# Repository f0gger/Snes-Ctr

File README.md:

# SNES Controller – KiCad Hardware Design

KiCad hardware design files for a custom Super Nintendo Entertainment System (SNES) controller built around the ATmega328P microcontroller, with I²C communication for interfacing with external devices.

## Repository Structure

```text
Snes-Ctr/
├── gerbers/ - Gerber and drill files for PCB manufacturing.
│   ├── Snes-Ctr-B_Cu.gbl
│   ├── Snes-Ctr-B_Mask.gbs
│   ├── Snes-Ctr-B_Paste.gbp
│   ├── Snes-Ctr-B_Silkscreen.gbo
│   ├── Snes-Ctr-Edge_Cuts.gm1
│   ├── Snes-Ctr-F_Cu.gtl
│   ├── Snes-Ctr-F_Mask.gts
│   ├── Snes-Ctr-F_Paste.gtp
│   ├── Snes-Ctr-F_Silkscreen.gto
│   ├── Snes-Ctr-NPTH.drl
│   ├── Snes-Ctr-PTH.drl
│   └── Snes_Ctr_gerbers.zip
├── Snes-Ctr.kicad_dru - Custom PCB design rules
├── Snes-Ctr.kicad_pcb - PCB layout.
├── Snes-Ctr.kicad_pro - KiCad project configuration.
├── Snes-Ctr.kicad_sch - Circuit schematic.
└── README.md
```

File names and structure may vary depending on the actual project files.
Hardware Overview

The controller uses the ATmega328P to interface with the SNES controller inputs and handle communication with external hardware over the I²C bus.

The KiCad project contains the circuit schematic and PCB design, providing a starting point for reviewing, modifying, and manufacturing the hardware.
Requirements

    KiCad — for viewing and editing the schematic and PCB
    ATmega328P-compatible programming hardware — for flashing firmware, if applicable

## Getting Started

    Clone this repository:
    git clone <repository-url>
    cd <repository-directory>
    
    Open the .kicad_pro file in KiCad.
    Review the schematic (.kicad_sch) to understand the circuit.
    Open the PCB editor to inspect or modify the board layout.
    Run the electrical rules check (ERC) and design rules check (DRC) before manufacturing.

## Manufacturing

Before ordering or assembling the PCB:

    - Verify the schematic and PCB design.
    - Check component footprints and pin assignments.
    - Run ERC and DRC in KiCad.
    - Generate Gerber files and drill files using KiCad's fabrication tools.
    - Confirm the bill of materials (BOM) and component availability.

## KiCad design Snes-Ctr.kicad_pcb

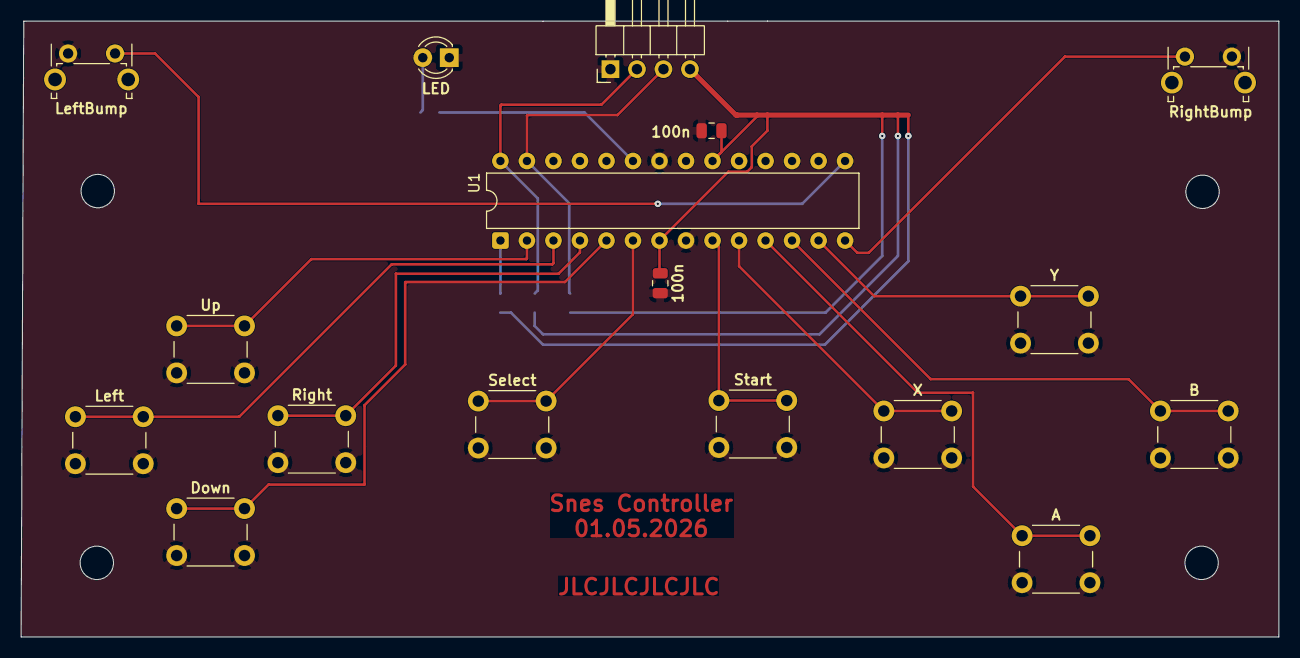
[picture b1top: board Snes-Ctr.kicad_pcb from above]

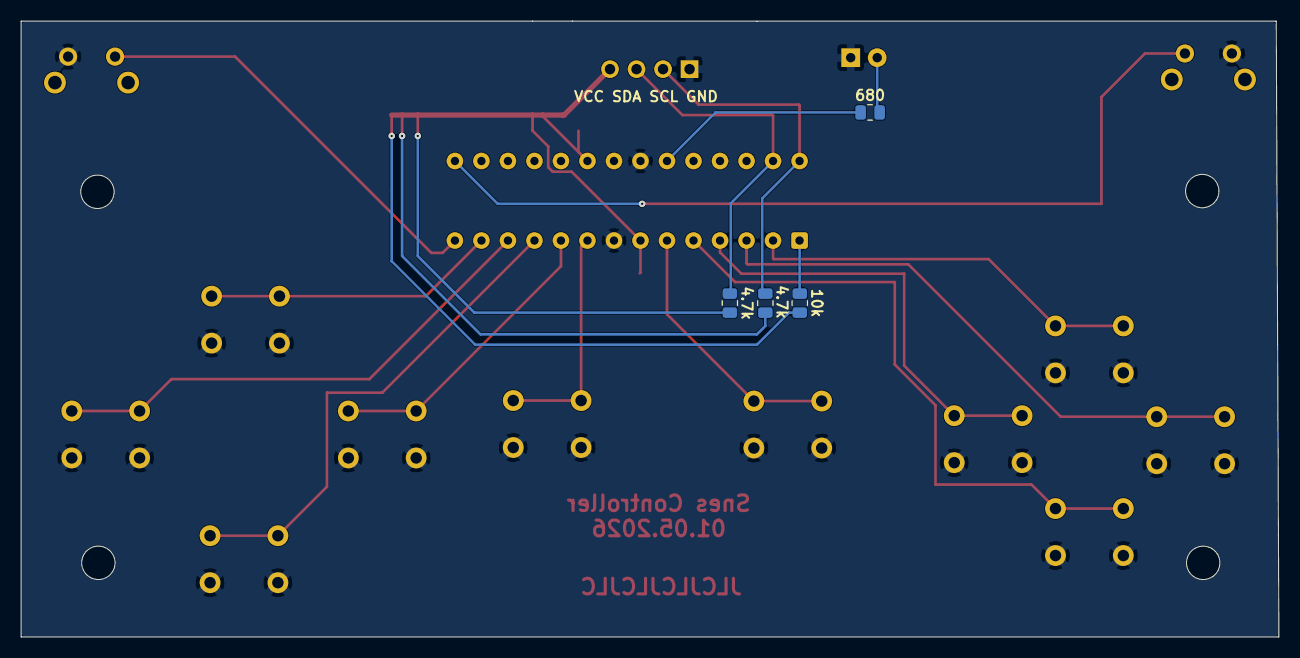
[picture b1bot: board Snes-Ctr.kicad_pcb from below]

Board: 2 copper layers, 120.5 x 59.0 mm, 21 parts (4 on the bottom side), 19 nets.

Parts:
4.7k, 4.7k#2: 4.7k; R_0805_2012Metric
10k: 10k; R_0805_2012Metric
100n, 100n#2: 100n; C_0805_2012Metric
680: 680; R_0805_2012Metric
A: A; SW_PUSH_6mm_H7.3mm
B: B; SW_PUSH_6mm_H7.3mm
Down: Down; SW_PUSH_6mm_H7.3mm
LED: LED; LED_D3.0mm
Left: Left; SW_PUSH_6mm_H7.3mm
LeftBump: Left Bumper; SW_Tactile_SPST_Angled_PTS645Vx58-2LFS
Right: Right; SW_PUSH_6mm_H7.3mm
RightBump: Right Bumper; SW_Tactile_SPST_Angled_PTS645Vx58-2LFS
Select: Select; SW_PUSH_6mm_H7.3mm
Start: Start; SW_PUSH_6mm_H7.3mm
U1: ATmega328-P; DIP-28_W7.62mm
Up: Up; SW_PUSH_6mm_H7.3mm
VCC SDA SCL GND: Conn_01x04_Pin; PinHeader_1x04_P2.54mm_Horizontal
X: X; SW_PUSH_6mm_H7.3mm
Y: Y; SW_PUSH_6mm_H7.3mm

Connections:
+3.3V: 4.7k.2, 4.7k#2.2, 10k.2, 100n.1, 100n#2.1, U1.7 (VCC), U1.20 (AVCC), VCC SDA SCL GND.4
GND: 100n.2, 100n#2.2, A.2 (A), B.2 (A), Down.2 (A), LED.1 (K), Left.2 (A), LeftBump.1 (A), Right.2 (A), RightBump.2 (A), Select.2 (A), Start.2 (A), U1.8 (GND), U1.22 (GND), Up.2 (A), VCC SDA SCL GND.1, X.2 (A), Y.2 (A)
unnamed: 680.2, LED.2 (A)
unnamed: 4.7k.1, U1.28 (PC5), VCC SDA SCL GND.2
unnamed: 4.7k#2.1, U1.27 (PC4), VCC SDA SCL GND.3
unnamed: RightBump.1 (A), U1.14 (PB0)
unnamed: LeftBump.2 (A), U1.15 (PB1)
unnamed: 680.1, U1.23 (PC0)
unnamed: U1.2 (PD0), Up.1 (A)
unnamed: Left.1 (A), U1.3 (PD1)
unnamed: Right.1 (A), U1.4 (PD2)
unnamed: Down.1 (A), U1.5 (PD3)
unnamed: Select.1 (A), U1.6 (PD4)
unnamed: A.1 (A), U1.11 (PD5)
unnamed: B.1 (A), U1.12 (PD6)
unnamed: U1.13 (PD7), Y.1 (A)
unnamed: Start.1 (A), U1.9 (XTAL1/PB6)
unnamed: U1.10 (XTAL2/PB7), X.1 (A)
unnamed: 10k.1, U1.1 (~RESET/PC6)

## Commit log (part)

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2026-06-20 online backup
